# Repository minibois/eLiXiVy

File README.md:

# mini-eLiXiVy
## Repository for the mini-eLiXiVy, a 65% mechanical keyboard PCB, suitable for ISO and ANSI layouts, USB Type C and a (tactile) rotary encoder.
 This PCB is compatible with KBDFans' 65% low profile case/plate and Cherry MX(-like) keyswitches.

 _Render of the front and back of the PCB respectively_

 << [License](https://github.com/minibois/eLiXiVy/blob/master/LICENSE/LICENSE.txt) || [Assembly Guide](https://github.com/minibois/eLiXiVy/blob/master/Documents/Assembly%20Guide.pdf) || BOM ([Octoparts](https://octopart.com/bom-tool/allQRgda)) / ([.txt](https://github.com/minibois/eLiXiVy/blob/master/Documents/BOM.txt)) / ([.xlsx](https://github.com/minibois/eLiXiVy/blob/master/Documents/BOM.xlsx)) || [Supported layouts](https://raw.githubusercontent.com/minibois/eLiXiVy/master/Documents/Layouts/layouts.png) || Schematic ([.pdf](https://github.com/minibois/eLiXiVy/blob/master/Documents/Schematic.pdf)) / ([.sch](https://github.com/minibois/eLiXiVy/blob/master/mini-eLiXiVy.sch)) || PCB ([.pdf](https://github.com/minibois/eLiXiVy/blob/master/Documents/PCB.pdf)) / ([.kicad_pcb](https://github.com/minibois/eLiXiVy/blob/master/mini-eLiXiVy.kicad_pcb)) >>

 The PCB and schematic are licensed under CERN-OHL-S v2, full license details can be found here: https://github.com/minibois/eLiXiVy/blob/master/Documents/LICENSE.txt.

### The compatible layouts for this PCB are as follows:

 _The mini-eLiXiVy supports between 66 and 69 switches, depending on the layout chosen._
 In the top right of the keyboard you can either use an MX-like keyswitch or a rotary encoder with switch (see the BOM for a verified compatible option).
 
 While the the bill of materials mentions tested compatible components, substitutes may be available, should these components become difficult to obtain. Should you choose alternatives, you do so at your own risk. I can only vouch for the compability of the listed components.

## Libraries used in this project (most of them adapted to this project):
 * That-Canadian's KiCad_labs (for the D-SOD123_axial-dual): https://github.com/That-Canadian/KiCad_Libs
 * Type-C.Pretty: https://github.com/ai03-2725/Type-C.pretty
 * MX_Alps_Hybrid: https://github.com/ai03-2725/MX_Alps_Hybrid
 * random-keyboard-parts (for a reset switch): https://github.com/ai03-2725/random-keyboard-parts.pretty

### This PCB file and schematic is provided - as per CERN-OHL-S v2 section 6 - _without any warranty_ (implied or otherwise). https://ohwr.org/cern_ohl_s_v2.pdf
### The assembly guide is provided under the CC BY-SA 4.0, without any warranty (implied or otherwise): https://creativecommons.org/licenses/by-sa/4.0/legalcode

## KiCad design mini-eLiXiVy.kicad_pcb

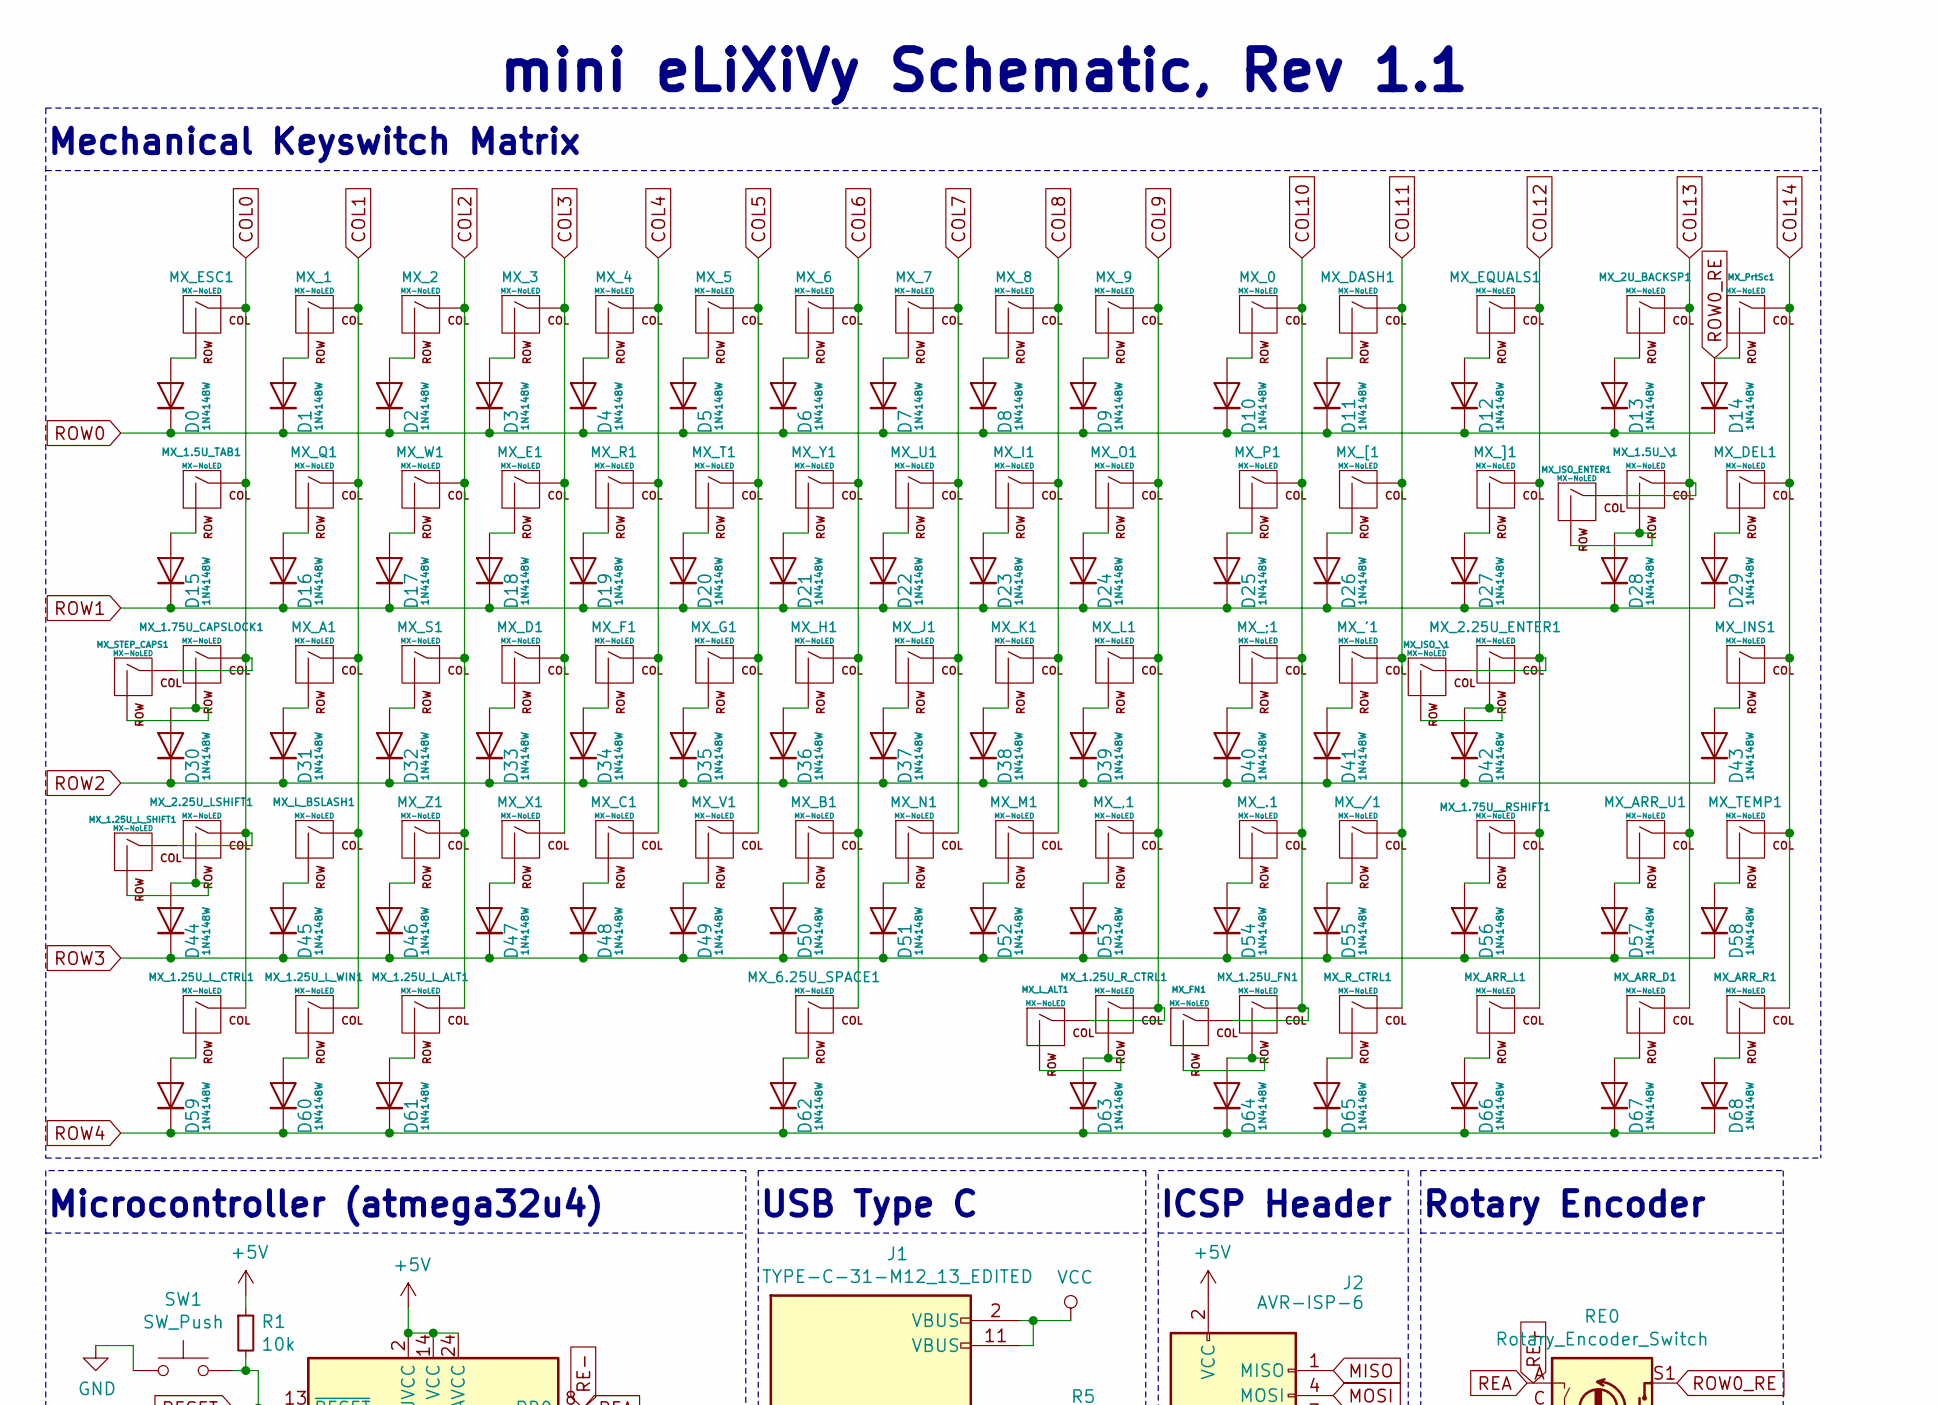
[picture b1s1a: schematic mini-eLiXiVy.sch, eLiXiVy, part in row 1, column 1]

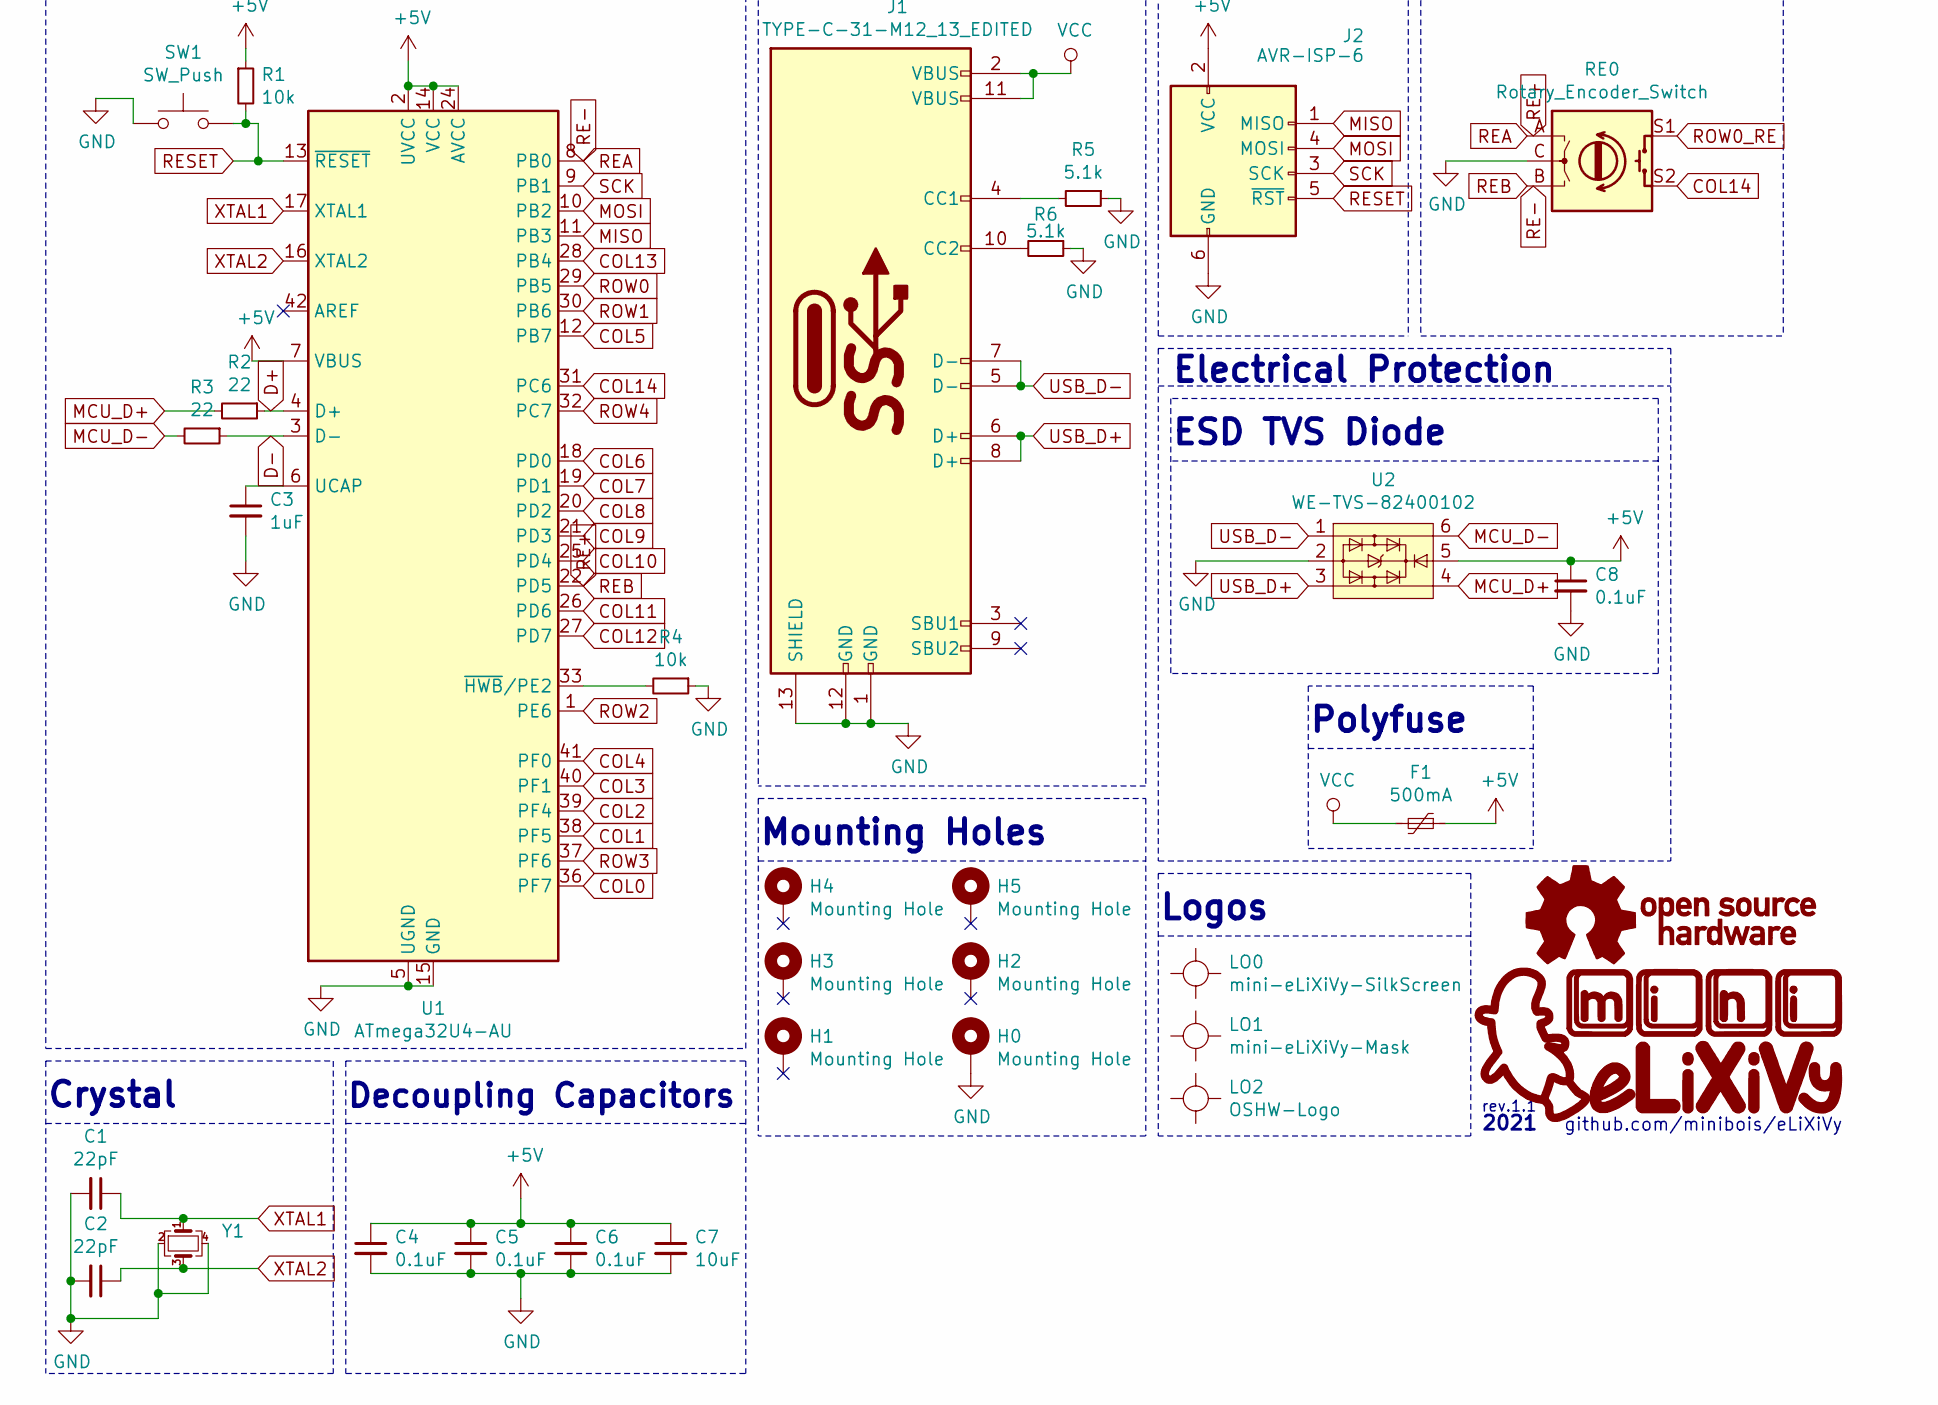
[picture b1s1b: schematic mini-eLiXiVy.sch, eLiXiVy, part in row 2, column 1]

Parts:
C1, C2: 22pF; C_0805_2012Metric
C3: 1uF; C_0805_2012Metric
C4, C5, C6, C8: 0.1uF; C_0805_2012Metric
C7: 10uF; C_0805_2012Metric
D0, D1, D2, D3, D4, D5, D6, D7, D8, D9, D10, D11, D12, D13, D14, D15, D16, D17, D18, D19, D20, D21, D22, D23, D24, D25, D26, D27, D28, D29, D30, D31, D32, D33, D34, D35, D36, D37, D38, D39, D40, D41, D42, D43, D44, D45, D46, D47, D48, D49, D50, D51, D52, D53, D54, D55, D56, D57, D58, D59, D60, D61, D62, D63, D64, D65, D66, D67, D68: 1N4148W; D_SOD123_axial-dual
F1: 500mA; Fuse_1206_3216Metric
H0, H1, H2, H3, H4, H5: Mounting Hole; MountingHole_2.2mm_M2_Pad_tweaked
J1: TYPE-C-31-M12_13_EDITED; HRO-TYPE-C-31-M-12-HandSoldering_tweaked
J2: AVR-ISP-6; ICSP_2.54mm_LAYOUT
LO0: mini-eLiXiVy-SilkScreen; eLiXiVy-rev1.1-SilkScreen
LO1: mini-eLiXiVy-Mask; eLiXiVy-rev1.1-Mask
LO2: OSHW-Logo
MX_0, MX_1, MX_2, MX_3, MX_4, MX_5, MX_6, MX_7, MX_8, MX_9, MX_.1: MX-NoLED; MXOnly-1U-NoLED_tweak
MX_1.5U_TAB1, MX_1.5U_\1: MX-NoLED; MXOnly-1.5U-NoLED_tweak
MX_1.25U_FN1, MX_1.25U_L_ALT1, MX_1.25U_L_CTRL1, MX_1.25U_L_SHIFT1, MX_1.25U_L_WIN1, MX_1.25U_R_CTRL1: MX-NoLED; MXOnly-1.25U-NoLED_tweak
MX_1.75U_CAPSLOCK1, MX_1.75U__RSHIFT1: MX-NoLED; MXOnly-1.75U-NoLED_tweak
MX_2.25U_ENTER1, MX_2.25U_LSHIFT1: MX-NoLED; MXOnly-2.25U-NoLED_tweak
MX_2U_BACKSP1: MX-NoLED; MXOnly-2U-NoLED_tweak
MX_6.25U_SPACE1: MX-NoLED; MXOnly-6.25U-ReversedStabilizers-NoLED_tweak
MX_'1: MX-NoLED; MXOnly-1U-NoLED_tweak
MX_,1: MX-NoLED; MXOnly-1U-NoLED_tweak
MX_/1: MX-NoLED; MXOnly-1U-NoLED_tweak
MX_;1: MX-NoLED; MXOnly-1U-NoLED_tweak
MX_A1: MX-NoLED; MXOnly-1U-NoLED_tweak
MX_ARR_D1: MX-NoLED; MXOnly-1U-NoLED_tweak
MX_ARR_L1: MX-NoLED; MXOnly-1U-NoLED_tweak
MX_ARR_R1: MX-NoLED; MXOnly-1U-NoLED_tweak
MX_ARR_U1: MX-NoLED; MXOnly-1U-NoLED_tweak
MX_B1: MX-NoLED; MXOnly-1U-NoLED_tweak
MX_C1: MX-NoLED; MXOnly-1U-NoLED_tweak
MX_D1: MX-NoLED; MXOnly-1U-NoLED_tweak
MX_DASH1: MX-NoLED; MXOnly-1U-NoLED_tweak
MX_DEL1: MX-NoLED; MXOnly-1U-NoLED_tweak
MX_E1: MX-NoLED; MXOnly-1U-NoLED_tweak
MX_EQUALS1: MX-NoLED; MXOnly-1U-NoLED_tweak
MX_ESC1: MX-NoLED; MXOnly-1U-NoLED_tweak
MX_F1: MX-NoLED; MXOnly-1U-NoLED_tweak
MX_FN1: MX-NoLED; MXOnly-1U-NoLED_tweak
MX_G1: MX-NoLED; MXOnly-1U-NoLED_tweak
MX_H1: MX-NoLED; MXOnly-1U-NoLED_tweak
MX_I1: MX-NoLED; MXOnly-1U-NoLED_tweak
MX_INS1: MX-NoLED; MXOnly-1U-NoLED_tweak
MX_ISO_ENTER1: MX-NoLED; MXOnly-ISO-ROTATED-ReversedStabilizers-NoLED_tweak
MX_ISO_\1: MX-NoLED; MXOnly-1U-NoLED_tweak
MX_J1: MX-NoLED; MXOnly-1U-NoLED_tweak
MX_K1: MX-NoLED; MXOnly-1U-NoLED_tweak
MX_L1: MX-NoLED; MXOnly-1U-NoLED_tweak
MX_L_ALT1: MX-NoLED; MXOnly-1U-NoLED_tweak
MX_L_BSLASH1: MX-NoLED; MXOnly-1U-NoLED_tweak
MX_M1: MX-NoLED; MXOnly-1U-NoLED_tweak
MX_N1: MX-NoLED; MXOnly-1U-NoLED_tweak
MX_O1: MX-NoLED; MXOnly-1U-NoLED_tweak
MX_P1: MX-NoLED; MXOnly-1U-NoLED_tweak
MX_PrtSc1: MX-NoLED; MXOnly-1U-NoLED_tweak
MX_Q1: MX-NoLED; MXOnly-1U-NoLED_tweak
MX_R1: MX-NoLED; MXOnly-1U-NoLED_tweak
MX_R_CTRL1: MX-NoLED; MXOnly-1U-NoLED_tweak
MX_S1: MX-NoLED; MXOnly-1U-NoLED_tweak
MX_STEP_CAPS1: MX-NoLED; MXOnly-1U-NoLED_tweak
MX_T1: MX-NoLED; MXOnly-1U-NoLED_tweak
MX_TEMP1: MX-NoLED; MXOnly-1U-NoLED_tweak
MX_U1: MX-NoLED; MXOnly-1U-NoLED_tweak
MX_V1: MX-NoLED; MXOnly-1U-NoLED_tweak
MX_W1: MX-NoLED; MXOnly-1U-NoLED_tweak
MX_X1: MX-NoLED; MXOnly-1U-NoLED_tweak
MX_Y1: MX-NoLED; MXOnly-1U-NoLED_tweak
MX_Z1: MX-NoLED; MXOnly-1U-NoLED_tweak
MX_[1: MX-NoLED; MXOnly-1U-NoLED_tweak
MX_]1: MX-NoLED; MXOnly-1U-NoLED_tweak
R1, R4: 10k; R_0805_2012Metric
R2, R3: 22; R_0805_2012Metric
R5, R6: 5.1k; R_0805_2012Metric
RE0: Rotary_Encoder_Switch; RotaryEncoder_Alps_EC11E-Switch-Vertical-EDIT
SW1: SW_Push; SKQG-1155865
U1: ATmega32U4-AU; TQFP-44_10x10mm_P0.8mm_ATmega32U4
U2: WE-TVS-82400102; SOT-23-6_tweaked
Y1: Crystal_GND24_Small; Crystal_SMD_3225-4Pin_3.2x2.5mm

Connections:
+5V: C4.1, C5.1, C6.1, C7.1, C8.1, F1.1, J2.2 (VCC), R1.1, U1.2 (UVCC), U1.7 (VBUS), U1.14 (VCC), U1.24 (AVCC), U1.34 (VCC), U1.44 (AVCC), U2.5
COL0: MX_1.5U_TAB1.1 (COL), MX_1.25U_L_CTRL1.1 (COL), MX_1.25U_L_SHIFT1.1 (COL), MX_1.75U_CAPSLOCK1.1 (COL), MX_2.25U_LSHIFT1.1 (COL), MX_ESC1.1 (COL), MX_STEP_CAPS1.1 (COL), U1.36 (PF7)
COL1: MX_1.1 (COL), MX_1.25U_L_WIN1.1 (COL), MX_A1.1 (COL), MX_L_BSLASH1.1 (COL), MX_Q1.1 (COL), U1.38 (PF5)
COL2: MX_1.25U_L_ALT1.1 (COL), MX_2.1 (COL), MX_S1.1 (COL), MX_W1.1 (COL), MX_Z1.1 (COL), U1.39 (PF4)
COL3: MX_3.1 (COL), MX_D1.1 (COL), MX_E1.1 (COL), MX_X1.1 (COL), U1.40 (PF1)
COL4: MX_4.1 (COL), MX_C1.1 (COL), MX_F1.1 (COL), MX_R1.1 (COL), U1.41 (PF0)
COL5: MX_5.1 (COL), MX_G1.1 (COL), MX_T1.1 (COL), MX_V1.1 (COL), U1.12 (PB7)
COL6: MX_6.1 (COL), MX_6.25U_SPACE1.1 (COL), MX_B1.1 (COL), MX_H1.1 (COL), MX_Y1.1 (COL), U1.18 (PD0)
COL7: MX_7.1 (COL), MX_J1.1 (COL), MX_N1.1 (COL), MX_U1.1 (COL), U1.19 (PD1)
COL8: MX_8.1 (COL), MX_I1.1 (COL), MX_K1.1 (COL), MX_M1.1 (COL), U1.20 (PD2)
COL9: MX_1.25U_R_CTRL1.1 (COL), MX_9.1 (COL), MX_,1.1 (COL), MX_L1.1 (COL), MX_L_ALT1.1 (COL), MX_O1.1 (COL), U1.21 (PD3)
COL10: MX_0.1 (COL), MX_1.25U_FN1.1 (COL), MX_.1.1 (COL), MX_;1.1 (COL), MX_FN1.1 (COL), MX_P1.1 (COL), U1.25 (PD4)
COL11: MX_'1.1 (COL), MX_/1.1 (COL), MX_DASH1.1 (COL), MX_R_CTRL1.1 (COL), MX_[1.1 (COL), U1.26 (PD6)
COL12: MX_1.75U__RSHIFT1.1 (COL), MX_2.25U_ENTER1.1 (COL), MX_ARR_L1.1 (COL), MX_EQUALS1.1 (COL), MX_ISO_\1.1 (COL), MX_]1.1 (COL), U1.27 (PD7)
COL13: MX_1.5U_\1.1 (COL), MX_2U_BACKSP1.1 (COL), MX_ARR_D1.1 (COL), MX_ARR_U1.1 (COL), MX_ISO_ENTER1.1 (COL), U1.28 (PB4)
COL14: MX_ARR_R1.1 (COL), MX_DEL1.1 (COL), MX_INS1.1 (COL), MX_PrtSc1.1 (COL), MX_TEMP1.1 (COL), RE0.S2, U1.31 (PC6)
D+: R2.1, U1.4 (D+)
D-: R3.1, U1.3 (D-)
GND: C1.2, C2.2, C3.2, C4.2, C5.2, C6.2, C7.2, C8.2, H0.1, J1.1 (GND), J1.12 (GND), J1.13 (SHIELD), J2.6 (GND), R4.1, R5.1, R6.1, RE0.C, SW1.1, U1.5 (UGND), U1.15 (GND), U1.23 (GND), U1.35 (GND), U1.43 (GND), U2.2, Y1.2, Y1.4
MCU_D+: R2.2, U2.4
MCU_D-: R3.2, U2.6
MISO: J2.1 (MISO), U1.11 (PB3)
MOSI: J2.4 (MOSI), U1.10 (PB2)
unnamed: C3.1, U1.6 (UCAP)
unnamed: D0.2 (A), MX_ESC1.2 (ROW)
unnamed: D1.2 (A), MX_1.2 (ROW)
unnamed: D2.2 (A), MX_2.2 (ROW)
unnamed: D3.2 (A), MX_3.2 (ROW)
unnamed: D4.2 (A), MX_4.2 (ROW)
unnamed: D5.2 (A), MX_5.2 (ROW)
unnamed: D6.2 (A), MX_6.2 (ROW)
unnamed: D7.2 (A), MX_7.2 (ROW)
unnamed: D8.2 (A), MX_8.2 (ROW)
unnamed: D9.2 (A), MX_9.2 (ROW)
unnamed: D10.2 (A), MX_0.2 (ROW)
unnamed: D11.2 (A), MX_DASH1.2 (ROW)
unnamed: D12.2 (A), MX_EQUALS1.2 (ROW)
unnamed: D13.2 (A), MX_2U_BACKSP1.2 (ROW)
unnamed: D15.2 (A), MX_1.5U_TAB1.2 (ROW)
unnamed: D16.2 (A), MX_Q1.2 (ROW)
unnamed: D17.2 (A), MX_W1.2 (ROW)
unnamed: D18.2 (A), MX_E1.2 (ROW)
unnamed: D19.2 (A), MX_R1.2 (ROW)
unnamed: D20.2 (A), MX_T1.2 (ROW)
unnamed: D21.2 (A), MX_Y1.2 (ROW)
unnamed: D22.2 (A), MX_U1.2 (ROW)
unnamed: D23.2 (A), MX_I1.2 (ROW)
unnamed: D24.2 (A), MX_O1.2 (ROW)
unnamed: D25.2 (A), MX_P1.2 (ROW)
unnamed: D26.2 (A), MX_[1.2 (ROW)
unnamed: D27.2 (A), MX_]1.2 (ROW)
unnamed: D28.2 (A), MX_1.5U_\1.2 (ROW), MX_ISO_ENTER1.2 (ROW)
unnamed: D29.2 (A), MX_DEL1.2 (ROW)
unnamed: D30.2 (A), MX_1.75U_CAPSLOCK1.2 (ROW), MX_STEP_CAPS1.2 (ROW)
unnamed: D31.2 (A), MX_A1.2 (ROW)
unnamed: D32.2 (A), MX_S1.2 (ROW)
unnamed: D33.2 (A), MX_D1.2 (ROW)
unnamed: D34.2 (A), MX_F1.2 (ROW)
unnamed: D35.2 (A), MX_G1.2 (ROW)
unnamed: D36.2 (A), MX_H1.2 (ROW)
unnamed: D37.2 (A), MX_J1.2 (ROW)
unnamed: D38.2 (A), MX_K1.2 (ROW)
unnamed: D39.2 (A), MX_L1.2 (ROW)
unnamed: D40.2 (A), MX_;1.2 (ROW)
unnamed: D41.2 (A), MX_'1.2 (ROW)
unnamed: D42.2 (A), MX_2.25U_ENTER1.2 (ROW), MX_ISO_\1.2 (ROW)
unnamed: D43.2 (A), MX_INS1.2 (ROW)
unnamed: D44.2 (A), MX_1.25U_L_SHIFT1.2 (ROW), MX_2.25U_LSHIFT1.2 (ROW)
unnamed: D45.2 (A), MX_L_BSLASH1.2 (ROW)
unnamed: D46.2 (A), MX_Z1.2 (ROW)
unnamed: D47.2 (A), MX_X1.2 (ROW)
unnamed: D48.2 (A), MX_C1.2 (ROW)
unnamed: D49.2 (A), MX_V1.2 (ROW)
unnamed: D50.2 (A), MX_B1.2 (ROW)
unnamed: D51.2 (A), MX_N1.2 (ROW)
unnamed: D52.2 (A), MX_M1.2 (ROW)
unnamed: D53.2 (A), MX_,1.2 (ROW)
unnamed: D54.2 (A), MX_.1.2 (ROW)
unnamed: D55.2 (A), MX_/1.2 (ROW)
unnamed: D56.2 (A), MX_1.75U__RSHIFT1.2 (ROW)
unnamed: D57.2 (A), MX_ARR_U1.2 (ROW)
unnamed: D58.2 (A), MX_TEMP1.2 (ROW)
unnamed: D59.2 (A), MX_1.25U_L_CTRL1.2 (ROW)
unnamed: D60.2 (A), MX_1.25U_L_WIN1.2 (ROW)
unnamed: D61.2 (A), MX_1.25U_L_ALT1.2 (ROW)
unnamed: D62.2 (A), MX_6.25U_SPACE1.2 (ROW)
unnamed: D63.2 (A), MX_1.25U_R_CTRL1.2 (ROW), MX_L_ALT1.2 (ROW)
unnamed: D64.2 (A), MX_1.25U_FN1.2 (ROW), MX_FN1.2 (ROW)
unnamed: D65.2 (A), MX_R_CTRL1.2 (ROW)
unnamed: D66.2 (A), MX_ARR_L1.2 (ROW)
unnamed: D67.2 (A), MX_ARR_D1.2 (ROW)
unnamed: D68.2 (A), MX_ARR_R1.2 (ROW)
unnamed: J1.4 (CC1), R5.2
unnamed: J1.10 (CC2), R6.2
unnamed: R4.2, U1.33 (~HWB~/PE2)
RE+: RE0.B, U1.22 (PD5)
RE-: RE0.A, U1.8 (PB0)
RESET: J2.5 (~RST), R1.2, SW1.2, U1.13 (~RESET)
ROW0: D0.1 (K), D1.1 (K), D2.1 (K), D3.1 (K), D4.1 (K), D5.1 (K), D6.1 (K), D7.1 (K), D8.1 (K), D9.1 (K), D10.1 (K), D11.1 (K), D12.1 (K), D13.1 (K), D14.1 (K), U1.29 (PB5)
ROW0_RE: D14.2 (A), MX_PrtSc1.2 (ROW), RE0.S1
ROW1: D15.1 (K), D16.1 (K), D17.1 (K), D18.1 (K), D19.1 (K), D20.1 (K), D21.1 (K), D22.1 (K), D23.1 (K), D24.1 (K), D25.1 (K), D26.1 (K), D27.1 (K), D28.1 (K), D29.1 (K), U1.30 (PB6)
ROW2: D30.1 (K), D31.1 (K), D32.1 (K), D33.1 (K), D34.1 (K), D35.1 (K), D36.1 (K), D37.1 (K), D38.1 (K), D39.1 (K), D40.1 (K), D41.1 (K), D42.1 (K), D43.1 (K), U1.1 (PE6)
ROW3: D44.1 (K), D45.1 (K), D46.1 (K), D47.1 (K), D48.1 (K), D49.1 (K), D50.1 (K), D51.1 (K), D52.1 (K), D53.1 (K), D54.1 (K), D55.1 (K), D56.1 (K), D57.1 (K), D58.1 (K), U1.37 (PF6)
ROW4: D59.1 (K), D60.1 (K), D61.1 (K), D62.1 (K), D63.1 (K), D64.1 (K), D65.1 (K), D66.1 (K), D67.1 (K), D68.1 (K), U1.32 (PC7)
SCK: J2.3 (SCK), U1.9 (PB1)
USB_D+: J1.6 (D+), J1.8 (D+), U2.3
USB_D-: J1.5 (D-), J1.7 (D-), U2.1
VCC: F1.2, J1.2 (VBUS), J1.11 (VBUS)
XTAL1: C1.1, U1.17 (XTAL1), Y1.1
XTAL2: C2.1, U1.16 (XTAL2), Y1.3

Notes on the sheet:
Decoupling Capacitors
Crystal
Mechanical Keyswitch Matrix
mini eLiXiVy Schematic, Rev 1.1
USB Type C
Mounting Holes
Electrical Protection
ESD TVS Diode
Polyfuse
Rotary Encoder
ICSP Header
Logos
github.com/minibois/eLiXiVy
rev.1.1
2021
Microcontroller (atmega32u4)

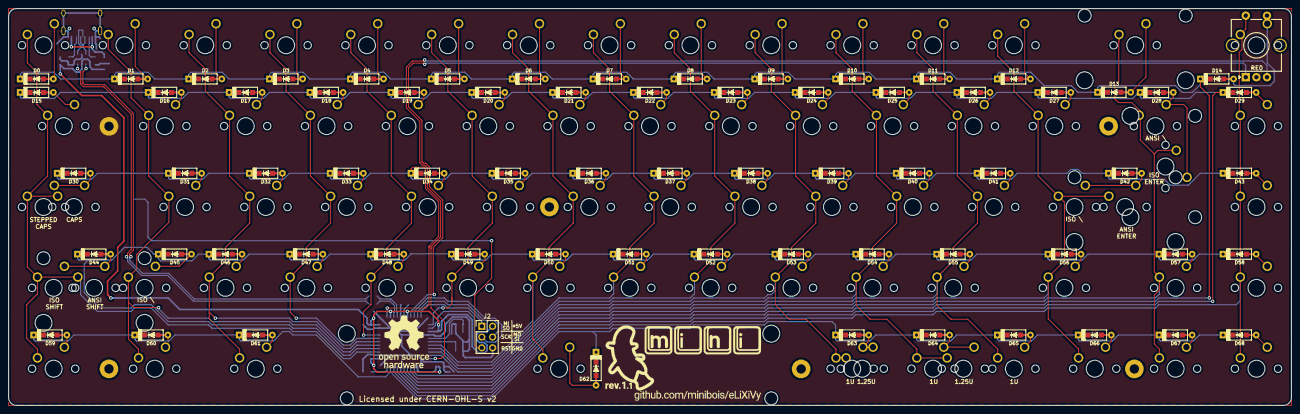
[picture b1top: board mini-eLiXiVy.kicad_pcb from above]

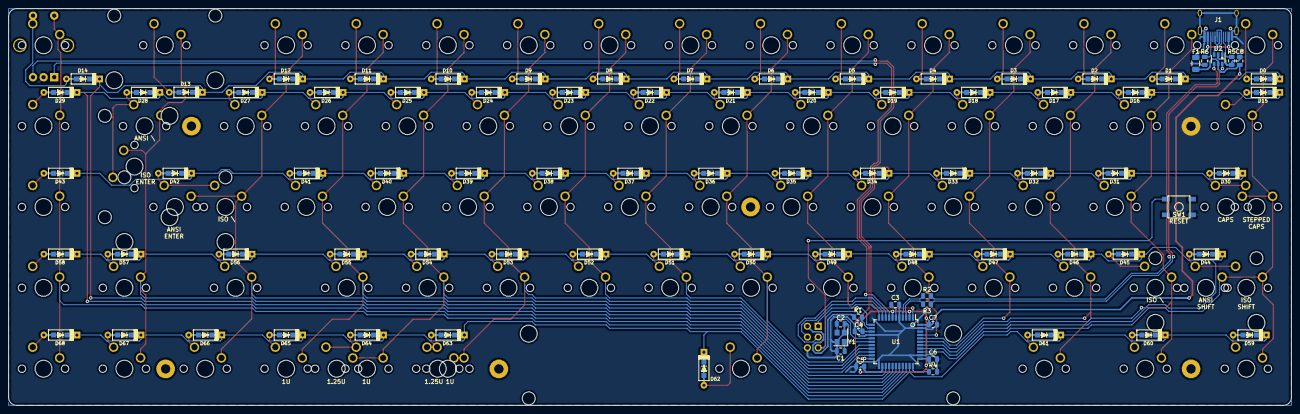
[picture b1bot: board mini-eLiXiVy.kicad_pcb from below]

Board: 2 copper layers, 302.2 x 93.5 mm, 175 parts (20 on the bottom side), 110 nets.

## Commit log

2020-07-20 Initialized the mini-65 project
2020-07-20 Added submodules
2020-07-20 Added libraries to SCH/PCB
2020-07-21 Added first switches
2020-07-21 layed down matrix for the keys
2020-07-21 Added ISP header
2020-07-21 Layed out most the schematic, sans ROW/COL nets
2020-07-21 Edited matrix look, adding extra keys now.
2020-07-22 Added all special keys to schematic
2020-07-22 Added unit measurement to all non-1U keys
2020-07-22 Moved around alternative keys in schematic to make it easier to read
2020-07-22 Readjusted some components on schematic
2020-07-22 Added Canadian Parts
2020-07-22 Annotated all components
2020-07-22 Added Canadian Submodule
2020-07-22 Applied some footprints, adjusted MX names.
    To make it easier to assign footprints, I added the U measurement to each key in the beginning of the name (MX_xU_KeyName).
2020-07-22 Assigned the last of the footprints
    Step before starting on the PCB. All footprints have been added.
2020-07-22 Imported everything from the sch to pcb
2020-07-22 Laid out keys on the PCB.
2020-07-22 Set MCU to the side
2020-07-23 Switched around ISO enter and ISO backslash
2020-07-23 Rearranged diodes
2020-07-23 changed location of diodes
2020-10-14 Moved around some of the diode locations
2020-10-15 Moved the diodes down a bit
2020-10-15 Routed all rows/colums, started on controller design
2020-10-16 Added additiona library, for JST connector
2020-10-16 Added symbols to project, for JST connector
2020-10-16 Added some libraries, to try to add JST connector
2020-10-17 Removed mini USB connector
2020-10-19 Laid out most of the MCU + JST connector
    Still have to finish up the ICSP header and reset switch and clean up some of the component placement and wiring.
2020-10-20 Routed everything, sans matrix
2020-10-20 Made most of the matrix, one issue left
    Unfortunately I didn't account for ROW1, meaning I didn't use one of the input pins.
    Still have to connect ROW1, now using the left over input pin.
2020-10-21 Finished the PCB matrix setup
2020-10-21 fucked it up
2020-10-21 Rerouted the first couple of columns
2020-10-22 Routed the MCU and the components around it
2020-10-22 Mostly routed, FORGOT COL13
2020-10-22 Routed up all the cols/rows, properly this time
2020-10-22 Routed most of the matrix
2020-10-22 Added the cols/rows to the MCU in the sch
2020-10-23 rerouted some of the lines
2020-11-24 before changing MCU position
2020-11-25 moved MCU left
    havent attached all routes yet
2021-03-26 Step before USB Type C connector
2021-03-27 Added USB Type C submodule
2021-03-28 Added USB Type C libraries
2021-03-28 Step before adding USB Type C connector
2021-03-29 Added USB Type C Archeron Library
2021-03-29 removed type C library, because it was only footprints
2021-03-29 Added USB Type C submodule library
2021-03-29 removed submodule
2021-03-29 Added Acheron Library, for the USB Type C Symbol
2021-03-29 Added new type C symbol to schematic
2021-03-30 Revert "Added new type C symbol to schematic"
    This reverts commit 1bda37eaa5b653feb19e23a5acef818b3a9bd8ba.
2021-03-31 Add ESD chip and wiring for it
2021-03-31 Wired up the ESD chip and placed everything in the right place
2021-04-01 Footprints assigned to schematic, step before changing the PCB up.
2021-04-20 USB Type C schematic library added
    Edited the nicer looking Type C symbol to support the Type C footprint
2021-04-20 routed some of the type C traces
2021-04-22 USB data lies routed
2021-04-23 Route most col/row traces
    Some col/row lines left, have to move up the MCU still.
2021-04-23 Most col/row lines are in place
2021-04-23 routed some more col/row lines
2021-04-23 All row/col lines route
2021-04-23 Added grounded screwholes to schematic/PCBq
    Still have to make sure it's grounded on all sides
2021-04-24 Tweaked ground plane, added col/rows to MCU
2021-04-24 All col/rows routed, ground screw pads extended
2021-04-24 Changed position of C5
2021-04-25 Rerouted +5V wire and placed fuse on the other side
2021-04-25 Step before printing
2021-04-27 Changed diode positions and misc. ground changes
2021-04-27 Tweaked the MX footprints to include plated holes
2021-04-28 exchanged MX models for the tweaked versions
2021-04-28 Updated PCB to tweaked footprints
2021-04-28 Tweaked footprints
2021-04-29 Restructured USB area, general silkscreen tweaks
2021-04-30 Added annotations under some multi compatibility keys
2021-05-05 general edits
2021-05-29 step before flipping all diodes
2021-05-31 Diodes in different place, row traces mostly ran.
2021-05-31 ran most column/row wires. about to change schematic
2021-06-03 misc changes, including ICSP silkscreen
2021-06-03 misc traces edits, change some col/row linkings
2021-06-04 misc changes
2021-06-08 changed USB routes
2021-06-13 updated schematic for fuse
2021-06-14 USB Type C routing
2021-06-16 minor tweaks to size of board and ground fill
2021-06-17 moved the screwholes around
2021-06-17 USB and screw holes are in the right location
2021-06-19 misc trace changes
2021-06-21 renamed diodes starting at 0
2021-06-22 Changed ESD chip, changed Type C routing
    ESD I wanted to order was not in stock, so I changed to a different part in the schematic.
    Upon reading the datasheet, it was made clear the +5V line has t pass through the ESD chip from one side to another, not merely run a trace into and out of it from one side.
2021-06-22 general routing tweaks
2021-07-02 Added the logo
    Added the logo to the symbol and footprint library, then added it to the schematic and then PCB.
    If the logo has to be edited, this should be done by replacing the footprint for it.
    Next step is adding a revision/version number to the logo itself.
    Maybe some silly 'made by' type of thing too.
2021-07-04 Added new version of logo
2021-07-04 changed layout of schematic
    started the cleanup of the schematic, with nice lines and names above parts
2021-07-05 Rearranged the schematic
    Added lines and text to the different parts of the schematic
2021-07-05 General schematic information added
2021-07-05 Added different OSHW logo
2021-07-06 moved H3 mounting hole
2021-07-06 Shrunk schematic/matrix to fit on an A4 sheet
2021-07-06 Rearranged the schematic to fit on an A4 sheet
2021-07-07 Added rotary encoder first steps
2021-07-07 Rearranged schematic, cleaned up RE lines
2021-07-07 Added OSHW and eLiXiVy logos to schematic
2021-07-08 Added LICENSE.txt
2021-07-08 Added LICENSE.txt and changed schematic text
2021-07-08 Made room for the GND plane between +5V/D+ & D-
2021-07-08 Step before changing all the files names
2021-07-08 Redid the names/rearranged the files
2021-07-09 Redid the library mentions
2021-07-09 Reconnected some of the traces
    After changing library locations around, some switches were disconnected in the schematic.
    Had to reconnect those.
2021-07-09 Reconnected a bunch of unconncted lines
2021-07-09 Reconncted a bunch of unconnected wires
2021-07-09 Reconnected some unconnected switches
2021-07-09 Merged with master
2021-07-09 Edited README and made the final gerber files
2021-07-11 Changed schematic's C8 100nF to 0.1uF (which are equal)
2021-07-13 Updated documentation
2021-07-13 Changed License locaiton
2021-07-13 Relocated LICENSE.txt
2021-07-13 Updated BOM.txt (and Octopart list)
2021-07-13 Removed extra empty line
2021-07-13 Added OHL license silkscreen.
    Added a "Licensed under CERN-OHL-S v2" silkscreen to the PCB, as per CERN-OHL-S v2, section 2.2.9.
2021-07-13 Update README.md
    Added the used libraries
2021-07-13 Added CHANGES.txt, full license and made LICENSE folder
2021-07-13 Change location of CHANGES, updated LICENSE and README
2021-07-13 Added BOM Excel file, edited BOM.txt
2021-07-13 Added images, adjusted README.md
2021-07-13 Adjusted layouts.png link
2021-07-13 Adjusted readme.md, including the list at the end.
2021-07-13 Replaced layout files, edited README
2021-07-15 Updated the README
2021-08-05 rev 1 changes
    Changed diode position for D62 and D13 (Spacebar and backspace).
    Removed the 'a' from the revision numbers, in the schematic and silkscreen art.
2021-08-05 Updated layout.json, to feature more information.
2021-08-10 Various changes
    - Changed rev.1a to rev.1
    - Tweaked layout.json and layout.png
    - Tweaked PCBPicture.png
    - Added QMK .hex and source
2021-08-10 Tweaked silkscreen
    Changed silkscreen layer for certain keyswitches, so it can be seen from the back what locations need to be used
2021-08-10 Updated readme.md
    Added links
2021-08-13 Updated schematic and PCB PDF versions, as well as tweaking the readme.
2021-08-17 Added the firmware and QMK config files
2021-08-17 Added layout images and README.md to layout folder
2021-08-17 Added the license as a README.md to the LICENSE folder
2021-08-18 Renamed the 'releases' folder to 'gerbers' and added the rev.1 gerbers
2021-08-18 rev.1a minor changes
2021-08-18 rev.1 gerbers made
2021-08-19 Added Assembly Guide, tweaked BOM tabs
2021-08-20 Changed R2/R3 location, redid D+/D- traces.
2021-08-21 Reran +5V and data lines
2021-08-22 Moved R2, R3 and rerouted data line/rotary encoder traces
2021-08-23 Updated logo, refined data line traces.
    Logos have been updated to match the revision number, rev.1.1
2021-08-24 Refined data line, rotary encoder and +5V traces
2021-08-25 Redid the rotary encoder traces
2021-11-17 Updated to rev.1.1

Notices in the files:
mini-eLiXiVy.kicad_pcb:
Full License: https://github.com/minibois/eLiXiVy/blob/master/LICENSE.txt
This PCB file describes Open Hardware and is licensed under the CERN-OHL-S v2.
mini-eLiXiVy.sch:
This schematic describes Open Hardware and is licensed under the CERN-OHL-S v2.
